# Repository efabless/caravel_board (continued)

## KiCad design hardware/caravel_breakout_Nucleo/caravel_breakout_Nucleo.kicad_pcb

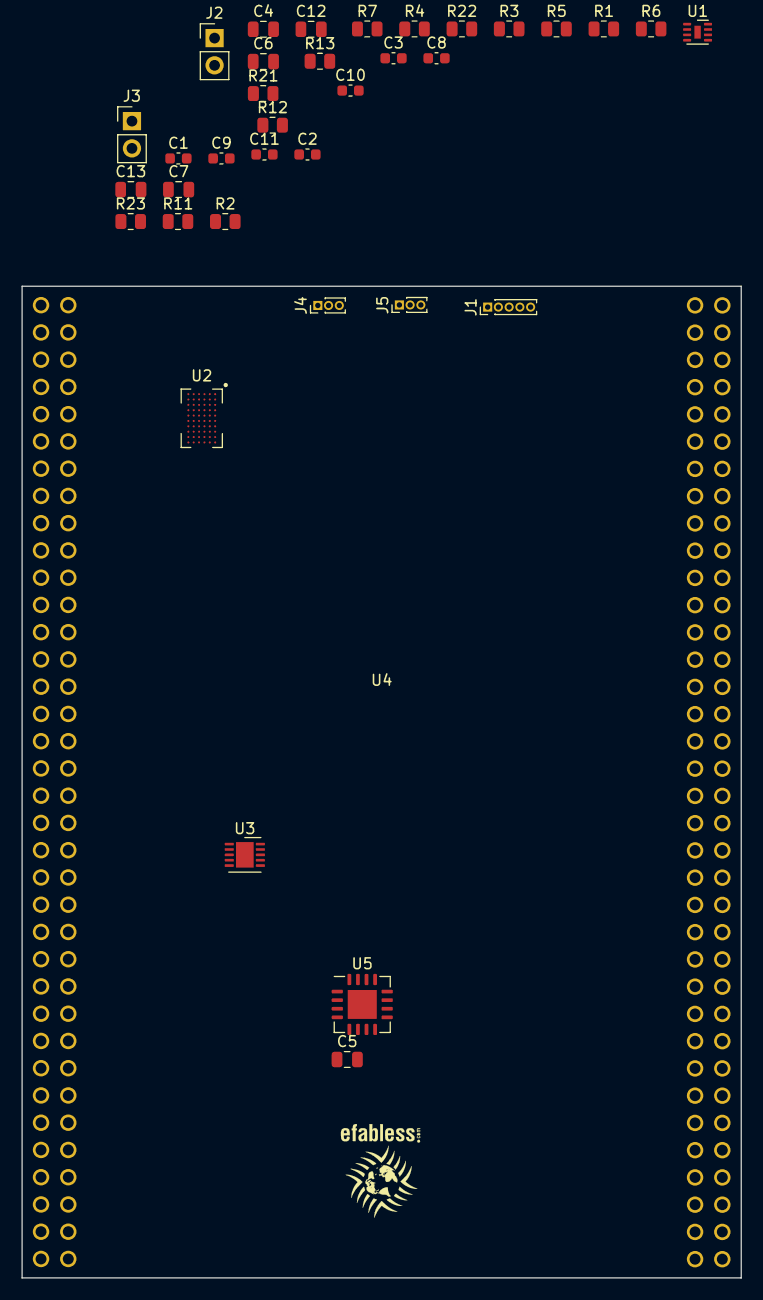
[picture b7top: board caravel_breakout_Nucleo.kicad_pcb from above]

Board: 2 copper layers, 67.0 x 92.4 mm, 38 parts (0 on the bottom side), 57 nets, no tracks yet.

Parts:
C1, C2, C3, C8, C9, C10, C11: 0.1uf; C_0603_1608Metric
C4, C5: 2.2uf - CC0805MKX5R6BB225; C_0805_2012Metric
C6, C12: 10uf - CC0805KKX5R8BB106; C_0805_2012Metric
C7, C13: 0.1uf - CC0805KRX7R9BB104; C_0805_2012Metric
J1: Conn_01x05_Female; PinHeader_1x05_P1.00mm_Vertical
J2, J3: Conn_01x02_Male; PinHeader_1x02_P2.54mm_Vertical
J4, J5: Conn_01x03; PinHeader_1x03_P1.00mm_Vertical
R1, R2, R3, R4, R5: 10k; R_0805_2012Metric
R6, R7: 4.7K 1% - 0805W8F1202T5E; R_0805_2012Metric
R11: 360 1% - 0805W8F1202T5E; R_0805_2012Metric
R12, R23: 4.99K 1% - 0805W8F1202T5E; R_0805_2012Metric
R13: 499 1% - 0805W8F1202T5E; R_0805_2012Metric
R21: 4.22K 1% - 0805W8F1202T5E; R_0805_2012Metric
R22: 4.02K 1% - 0805W8F1202T5E; R_0805_2012Metric
T1: Logo; logo
T2: Logo; ef_logo
U1: MIC5350-SGYMT-TR; DFN-8-1EP_2x2mm_P0.5mm_EP0.6x1.2mm
U2: Caravel; Caravel_WCSP
U3: MIC2211-AAYML-TR; DFN-10-1EP_3x3mm_P0.5mm_EP1.65x2.38mm
U4: NUCLEO144-F429ZI; ST_Morpho_Connectors_144
U5: MCP4661; QFN-16-1EP_5x5mm_P0.8mm_EP2.7x2.7mm

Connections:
+5V: C6.2, C12.2, R1.2, R2.2, R3.2, R4.2, R5.2, R6.1, R7.1, U1.1 (VIN), U3.1 (VIN), U4.18 (+5V), U5.7 (P1A), U5.8 (P0A), U5.14 (VDD)
Caravel_CSB: U2.C10 (flash_csb), U4.128 (PE11)
Caravel_D0: U2.D10 (flash_io0), U4.123 (PE14)
Caravel_D1: U2.D9 (flash_io1), U4.127 (PE13)
Caravel_SCK: U2.D8 (flash_clk), U4.121 (PE12)
GND: C1.2, C2.1, C3.2, C4.1, C5.1, C6.1, C7.2, C8.1, C9.1, C10.1, C11.1, C12.1, C13.2, R12.1, R22.1, U1.2 (GND), U1.9 (GND), U2.B3 (vssa2), U2.B7 (vssd2), U2.C5 (vssa/vssd/vssio), U2.C6 (vssa/vssd/vssio), U2.D5 (vssa/vssd/vssio), U2.D6 (vssa/vssd/vssio), U2.E6 (vssa1), U2.F6 (vssd1), U3.6 (GND), U4.8 (GND), U4.19 (GND), U4.20 (GND), U4.22 (GND), U4.49 (GND), U4.60 (GND), U4.71 (GND), U4.72 (GND), U4.81 (GND), U4.92 (GND), U4.104 (AGND), U4.111 (GND), U4.126 (GND), U4.135 (GND), U4.143 (GND), U4.144 (GND), U5.1 (HVC/A0), U5.4 (VSS), U5.5 (P1B), U5.10 (P0B), U5.12 (A2), U5.13 (A1)
I2C2_SCL: R7.2, U4.51 (PF1), U5.2 (SCL)
I2C2_SDA: R6.2, U4.53 (PF0), U5.3 (SDA)
unnamed: C7.1, U1.3 (BYP)
unnamed: C13.1, U3.4 (BYP)
unnamed: R1.1, U1.5 (EN1)
unnamed: R2.1, U1.4 (EN2)
unnamed: R3.1, U3.2 (EN1)
unnamed: R4.1, U3.3 (EN2)
unnamed: R5.1, U5.11 (~WP)
unnamed: R11.1, R12.2, R13.2, U3.5 (ADJ1)
unnamed: R13.1, U5.9 (P0W)
unnamed: R21.1, R22.2, R23.2, U3.7 (ADJ2)
unnamed: R23.1, U5.6 (P1W)
PC0: U2.E2 (mprj_io[14]), U4.38 (PC0)
PC8: U2.A3 (mprj_io[25]), U2.A9 (mprj_io[37])
PC9: U2.B9 (mprj_io[36]), U4.73 (PC9)
PD3: U2.E1 (mprj_io[16]), U4.40 (PD3)
PD4: U2.F1 (mprj_io[15]), U4.39 (PD4)
PD5: U2.D2 (mprj_io[17]), U4.41 (PD5)
PD6: U2.C1 (mprj_io[19]), U4.43 (PD6)
PD7: U2.B1 (mprj_io[21]), U4.45 (PD7)
PG0: U2.A1 (mprj_io[23]), U4.59 (PG0)
PG1: U2.B2 (mprj_io[22]), U4.58 (PG1)
PG2: U2.D1 (mprj_io[18]), U4.42 (PG2)
PG3: U2.C2 (mprj_io[20]), U4.44 (PG3), U4.64 (PG15)
SPI5_CS: U2.E8 (mprj_io[3]_CSB), U4.9 (PF6)
SPI5_MISO: U2.F9 (mprj_io[2]_SDI), U4.54 (PF8)
SPI5_MOSI: U2.E9 (mprj_io[1]_SDO), U4.56 (PF9)
SPI5_SCK: U2.F8 (mprj_io[4]_SCK), U4.11 (PF7)
TIM3_CH2: J1.4, U2.C9 (clock), U4.101 (PB5)
UART3_RX: U2.F7 (mprj_io[6]_ser_tx), U4.2 (PC11)
UART3_TX: U2.E7 (mprj_io[5]_ser_rx), U4.1 (PC10)
V1.8: C5.2, J4.1, U1.7 (VOUT2)
V3.3: C4.2, J5.1, U1.8 (VOUT1)
VOUT1: J5.3, R11.2, U3.10 (VOUT1)
VOUT2: J4.3, R21.2, U3.9 (VOUT2)
gpio: J1.3, U2.E10 (gpio)
mprj_io[0]: U2.D7 (mprj_io[0]_JTAG), U4.37 (PC3)
mprj_io[7]: U2.E5 (mprj_io[7]_IRQ), U4.35 (PC2)
mprj_io[8]: U2.F5 (mprj_io[8]_flash_csb), U4.32 (PA4)
mprj_io[9]: U2.E4 (mprj_io[9]_flash2_sck), U4.28 (ETH_REF_CLK/PA0)
mprj_io[10]: U2.F4 (mprj_io[10]_flash_io0), U4.17 (PA15)
mprj_io[11]: U2.E3 (mprj_io[11]_flash2_io1), U4.15 (TCK/PA14)
mprj_io[12]: U2.F3 (mprj_io[12]), U4.13 (TMS/PA13)
mprj_io[13]: U2.D3 (mprj_io[13]), U4.4 (PD2)
vccd: C2.2, C8.2, J3.1, J3.2, J4.2, U2.A10 (vccd), U2.F2 (vccd1)
vccd2: C9.2, J1.2, U2.A2 (vccd2)
vdda: C3.1, C10.2, J2.1, J2.2, J5.2, U2.C4 (vddio), U2.F10 (vdda)
vdda1: C1.1, J1.5, U2.D4 (vdda1)
vdda2: C11.2, J1.1, U2.C7 (vdda2)
~RST: U2.B10 (resetb), U4.14 (~RST)
